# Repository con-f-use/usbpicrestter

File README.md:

USBPicResetter
=================

This is a small board and firmware for resetting USB power periodically.
It utilizes a
[Microchip](http://www.microchip.com/)
[PIC10F200/202/204/206](http://ww1.microchip.com/downloads/en/DeviceDoc/41239D.pdf)
micro controller. The board design was done in
[KiCad](http://www.kicad-pcb.org/). You can
[order it at OSH Park](https://oshpark.com/shared_projects/06gSpBy6) in its
earlier version without the improved silkscreen (three for $5 + comonent
costs). The firmware can be compiled with the XC8 compiler via the
[MPLAB IDE](http://www.microchip.com/pagehandler/en-us/family/mplabx/).
Both tools should be free as in free beer. The layout was intended to be home
etched (single sided). The PIC10F200 can be had on Aliexpress for under 20
cents.

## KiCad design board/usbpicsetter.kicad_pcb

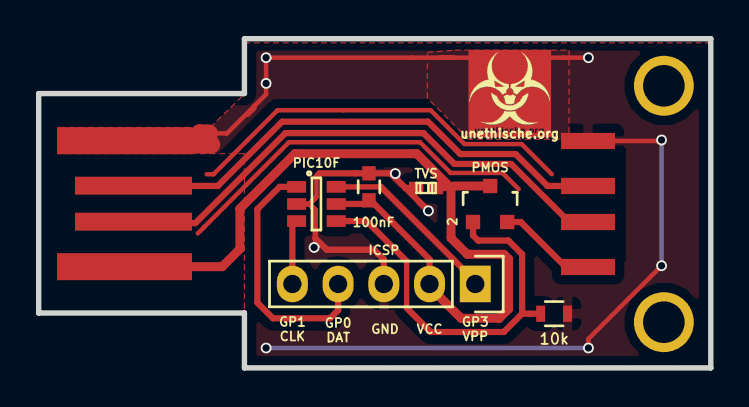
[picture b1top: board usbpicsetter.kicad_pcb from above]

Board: 2 copper layers, 37.3 x 18.3 mm, 10 parts (1 on the bottom side), 9 nets.

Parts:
C1: 100nF; C_0603
D1: TVS; r_0402
IC1: PIC10F; SOT-23-6
LOGO1: open hardware; Logo_silk_OSHW_6x6mm
O1: unethische.org; unethi_copper_inv
P1: ICSP; Pin_Header_Straight_1x05
Q1: PMOS; SOT-23
R1: 10k; R_0603
USB-IN1: Male; USB-A-PCB
USB_OUT1: Female; USB-A-S-NOSILK-FEMALE

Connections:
/CLK: IC1.3, P1.5
/D+: USB-IN1.3, USB_OUT1.3
/D-: USB-IN1.2, USB_OUT1.2
/DAT: IC1.1, P1.4
/PSW: IC1.4, Q1.1, R1.2
/VPP: IC1.6, P1.1
/Vout: Q1.2, USB_OUT1.1
GND: C1.2, D1.2, IC1.2, P1.3, R1.1, USB-IN1.4, USB_OUT1.4
VCC: C1.1, D1.1, IC1.5, P1.2, Q1.3, USB-IN1.1

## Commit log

2015-09-09 Improved silk screen, generated gerbers and modified C programm
2015-10-04 Added labels

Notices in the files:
board/usbpicsetter.kicad_pcb:
public domain.
